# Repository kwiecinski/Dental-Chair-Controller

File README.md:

### UP/DOWN controller for dental chair

- PCB: KiCad v5.1.5
- Code build in MPLAB X IDE v5.30, XC8 compiler v2.10 (free version)

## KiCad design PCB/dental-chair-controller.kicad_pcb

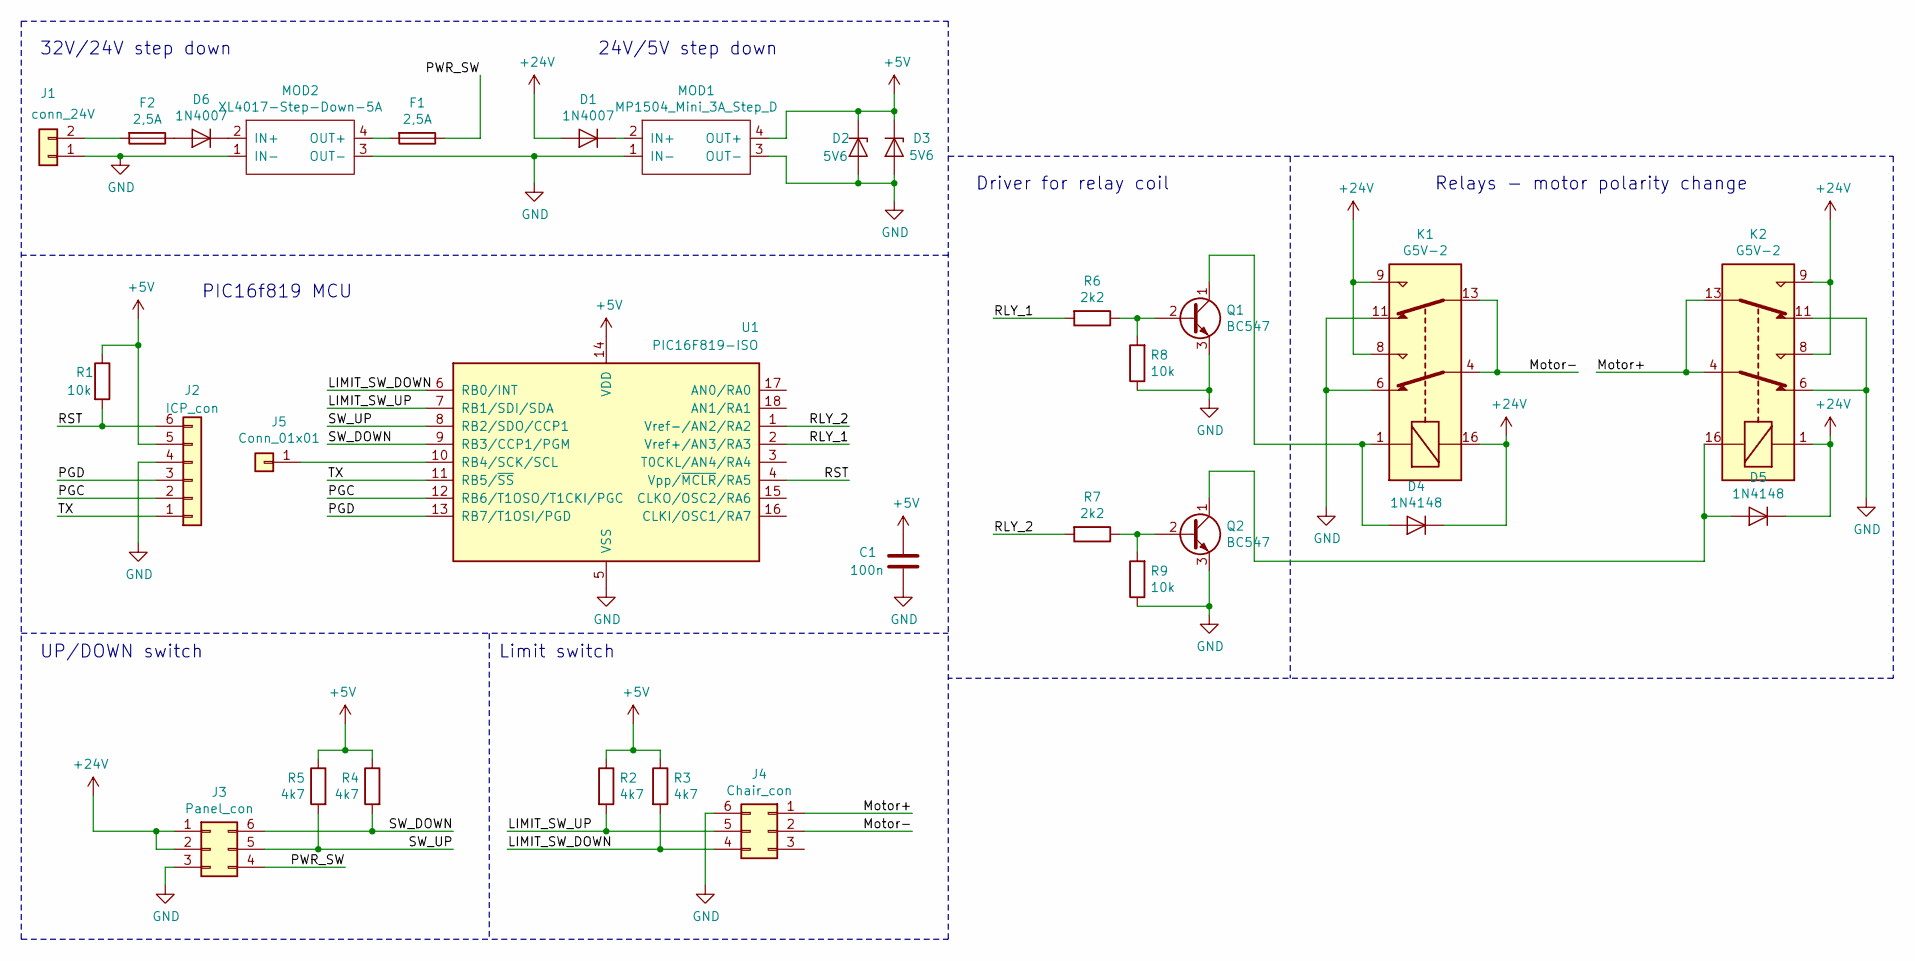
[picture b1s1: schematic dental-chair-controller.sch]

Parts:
C1: 100n; C_0805_HandSoldering
D1, D6: 1N4007; D_DO-41_SOD81_P10.16mm_Horizontal
D2, D3: 5V6; D_DO-35_SOD27_P7.62mm_Horizontal
D4, D5: 1N4148; R_0805_HandSoldering
F1, F2: 2,5A; Fuseholder5x20_horiz_SemiClosed_Casing10x25mm
J1: conn_24V; Conn_1x2_wire
J2: ICP_con; Pin_Header_Straight_1x06_Pitch2.54mm
J3: Panel_con; Molex_MegaFit_2x03x5.70mm_Straight
J4: Chair_con; Molex_MegaFit_2x03x5.70mm_Straight
J5: Conn_01x01; WIRE_PAD_1,3mm
K1, K2: G5V-2; Relay_29mm
MOD1: MP1504_Mini_3A_Step_D; MP1504_Mini_3A_Step_Down_Conv
MOD2: XL4017-Step-Down-5A
Q1, Q2: BC547; TO-92_Inline_Wide
R1, R8, R9: 10k; R_0805_HandSoldering
R2, R3, R4, R5: 4k7; R_0805_HandSoldering
R6, R7: 2k2; R_0805_HandSoldering
U1: PIC16F819-ISO; SOIC-18W_7.5x11.6mm_Pitch1.27mm

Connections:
+5V: C1.1, D2.1 (K), D3.1 (K), J2.5, MOD1.4 (OUT+), R1.1, R2.1, R3.1, R4.1, R5.1, U1.14 (VDD)
+24V: D1.2 (A), D4.1 (K), D5.1 (K), J3.1, J3.2, K1.8, K1.9, K1.16, K2.1, K2.8, K2.9
/LIMIT_SW_DOWN: J4.4, R3.2, U1.6 (RB0/INT)
/LIMIT_SW_UP: J4.5, R2.2, U1.7 (RB1/SDI/SDA)
/Motor+: J4.1, K2.4, K2.13
/Motor-: J4.2, K1.4, K1.13
/PGC: J2.2, U1.12 (RB6/T1OSO/T1CKI/PGC)
/PGD: J2.3, U1.13 (RB7/T1OSI/PGD)
/PWR_SW: F1.1, J3.4
/RLY_1: R6.2, U1.2 (Vref+/AN3/RA3)
/RLY_2: R7.2, U1.1 (Vref-/AN2/RA2)
/RST: J2.6, R1.2, U1.4 (Vpp/~MCLR~/RA5)
/SW_DOWN: J3.6, R4.2, U1.9 (RB3/CCP1/PGM)
/SW_UP: J3.5, R5.2, U1.8 (RB2/SDO/CCP1)
/TX: J2.1, U1.11 (RB5/~SS~)
GND: C1.2, D2.2 (A), D3.2 (A), J1.1, J2.4, J3.3, J4.6, K1.6, K1.11, K2.6, K2.11, MOD1.1 (IN-), MOD1.3 (OUT-), MOD2.1 (IN-), MOD2.3 (OUT-), Q1.3 (E), Q2.3 (E), R8.1, R9.1, U1.5 (VSS)
unnamed: D1.1 (K), MOD1.2 (IN+)
unnamed: D4.2 (A), K1.1, Q1.1 (C)
unnamed: D5.2 (A), K2.16, Q2.1 (C)
unnamed: D6.1 (K), MOD2.2 (IN+)
unnamed: D6.2 (A), F2.1
unnamed: F1.2, MOD2.4 (OUT+)
unnamed: F2.2, J1.2
unnamed: J5.1, U1.10 (RB4/SCK/SCL)
unnamed: Q1.2 (B), R6.1, R8.2
unnamed: Q2.2 (B), R7.1, R9.2

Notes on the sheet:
Limit switch
UP/DOWN switch
32V/24V step down
24V/5V step down
PIC16f819 MCU
Driver for relay coil
Relays - motor polarity change

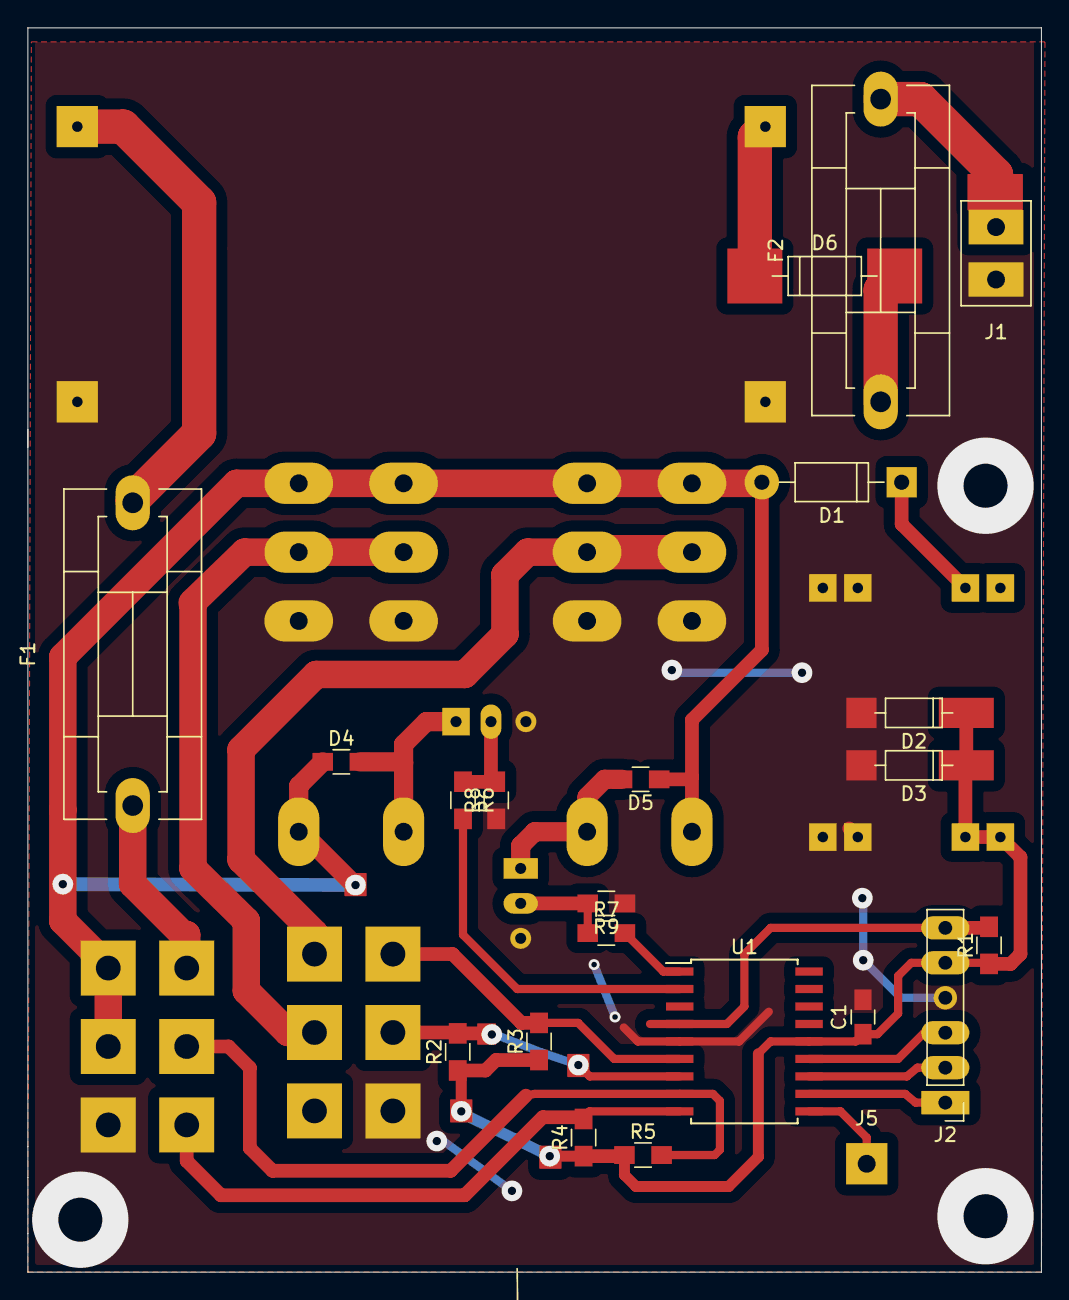
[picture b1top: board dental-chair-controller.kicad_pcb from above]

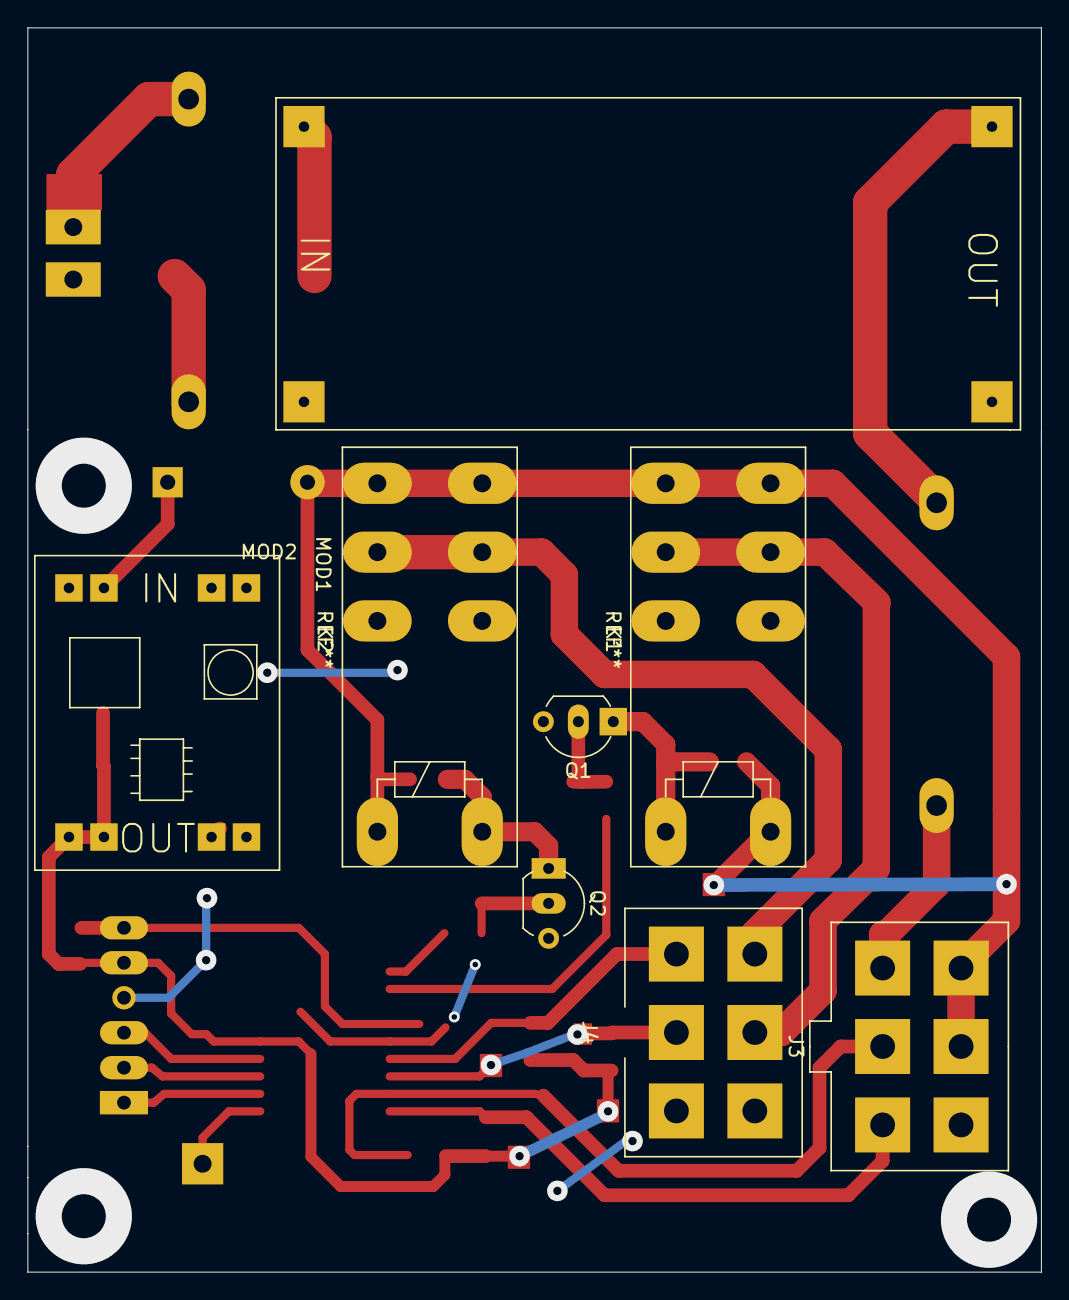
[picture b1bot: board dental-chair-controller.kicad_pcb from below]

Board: 2 copper layers, 73.7 x 90.4 mm, 30 parts (8 on the bottom side), 26 nets.

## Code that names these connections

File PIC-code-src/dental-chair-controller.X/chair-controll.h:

#ifndef CHAIR_CONTROLL_H
#define	CHAIR_CONTROLL_H

#include "define.h"

#define	SW_UP				PORTBbits.RB2
#define	SW_DOWN				PORTBbits.RB3

#define	LIMIT_SW_DOWN		PORTBbits.RB0
#define	LIMIT_SW_UP			PORTBbits.RB1

#define RELAY_UP_ON         PORTAbits.RA3=1          
#define RELAY_UP_OFF        PORTAbits.RA3=0 

#define RELAY_DOWN_ON       PORTAbits.RA2=1 
#define RELAY_DOWN_OFF      PORTAbits.RA2=0



void DownKeyPress(FLAGS *ptrflag);
void UpKeyPress(FLAGS *ptrflag);
void CheckFlagStatus(FLAGS *ptrflag);
void DownLimitSW(FLAGS *ptrflag);
void UpLimitSW(FLAGS *ptrflag);

#endif	/* CHAIR_CONTROLL_H */
